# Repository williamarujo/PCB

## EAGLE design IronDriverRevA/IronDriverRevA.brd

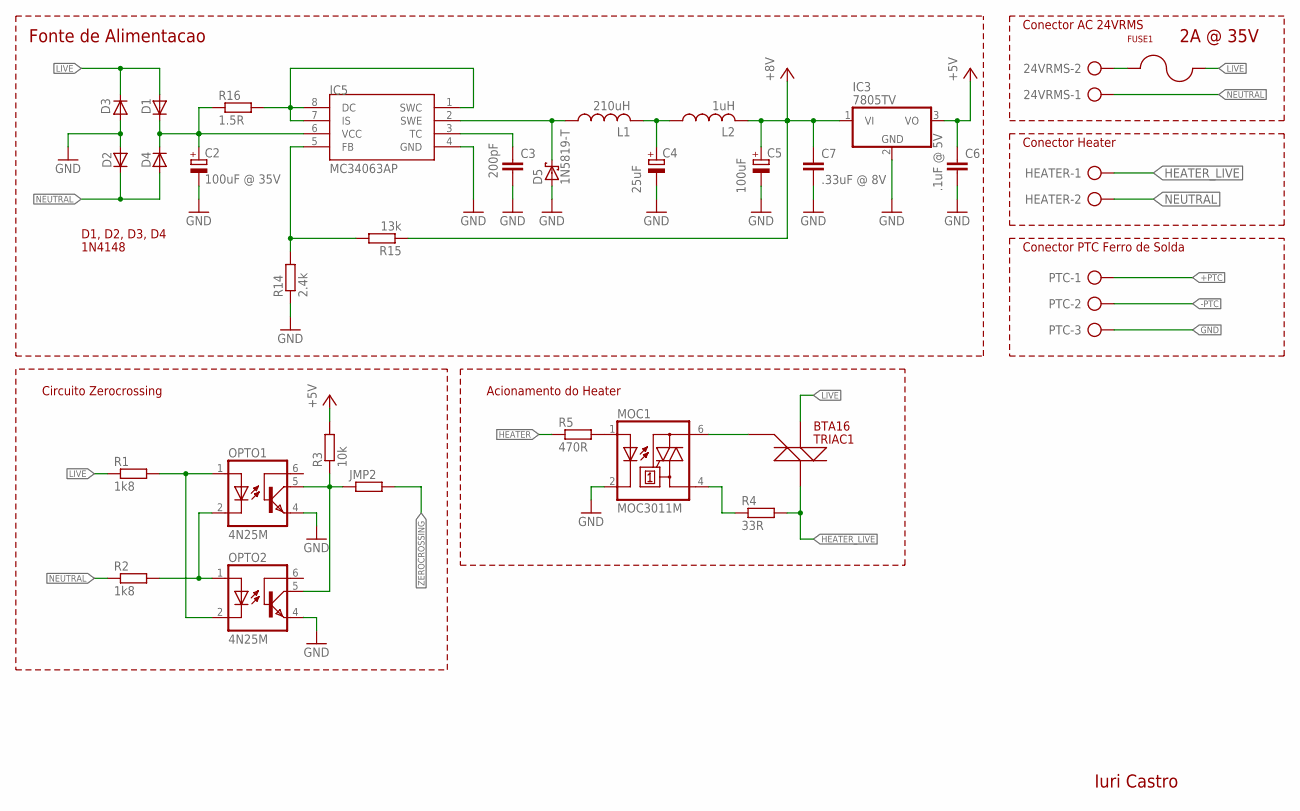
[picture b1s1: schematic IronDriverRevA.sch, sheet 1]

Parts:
24VRMS: AK500/2
C2: 100uF @ 35V; E3,5-8
C3: 200pF; C025-025X050
C4: 25uF; E3,5-8
C5: 100uF; E3,5-8
C6: .1uF @ 5V; C025-025X050
C7: .33uF @ 8V; C025-025X050
D1, D2, D3, D4: 1N4004; DO41-10
D5: 1N5819-T; DO41-7.6
FUSE1: FUSEHOLDER; FUSE32V2A5
HEATER: AK500/2
IC3: 7805TV; TO220V
IC5: MC34063AP; DIL08
JMP2: R-EU_R1206; R1206
L1: 210uH; 6000-XXXX-RC
L2: 1uH; 0204/7
MOC1: MOC3011M; DIL06
OPTO1, OPTO2: 4N25M; DIL06
PTC: AK500/3
R1, R2: 1k8; 0207/7
R3: 10k; 0207/7
R4: 33R; 0207/7
R5: 470R; 0207/7
R14: 2.4k; 0207/7
R15: 13k; 0207/7
R16: 1.5R; 0207/7
TRIAC1: BTA16; TO220V

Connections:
+5V: C6.1, IC3.3 (VO), R3.2; also elsewhere on the board
+8V: C5.+, C7.1, IC3.1 (VI), L2.2, R15.1; also elsewhere on the board
+PTC: PTC.1; also elsewhere on the board
-PTC: PTC.2; also elsewhere on the board
GND: C2.-, C3.2, C4.-, C5.-, C6.2, C7.2, D2.A, D3.A, D5.A, IC3.2 (GND), IC5.4 (GND), MOC1.2 (C), OPTO1.4 (EMI), OPTO2.4 (EMI), PTC.3, R14.1; also elsewhere on the board
HEATER: R5.1; also elsewhere on the board
HEATER_LIVE: HEATER.1, R4.2, TRIAC1.2 (A2)
LIVE: D1.A, D3.C, FUSE1.P$3, FUSE1.P$4, R1.1, TRIAC1.1 (A1)
unnamed: MOC1.1 (A), R5.2
unnamed: OPTO1.2 (C), OPTO2.1 (A), R2.2
unnamed: OPTO1.1 (A), OPTO2.2 (C), R1.2
unnamed: MOC1.6 (A2), TRIAC1.3 (G)
unnamed: MOC1.4 (A1), R4.1
unnamed: 24VRMS.2, FUSE1.P$1, FUSE1.P$2
unnamed: D5.C, IC5.2 (SWE), L1.1
unnamed: IC5.5 (FB), R14.2, R15.2
unnamed: IC5.1 (SWC), IC5.7 (IS), IC5.8 (DC), R16.2
unnamed: C4.+, L1.2, L2.1
unnamed: C3.1, IC5.3 (TC)
unnamed: C2.+, D1.C, D4.C, IC5.6 (VCC), R16.1
NEUTRAL: 24VRMS.1, D2.C, D4.A, HEATER.2, R2.1
ZEROCROSSING: JMP2.2; also elsewhere on the board
ZEROCROSSING_B: JMP2.1, OPTO1.5 (COL), OPTO2.5 (COL), R3.1

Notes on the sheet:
Conector AC 24VRMS
Conector PTC Ferro de Solda
Conector Heater
Circuito Zerocrossing
Acionamento do Heater
D1, D2, D3, D4
1N4148
Iuri Castro
2A @ 35V
Fonte de Alimentacao

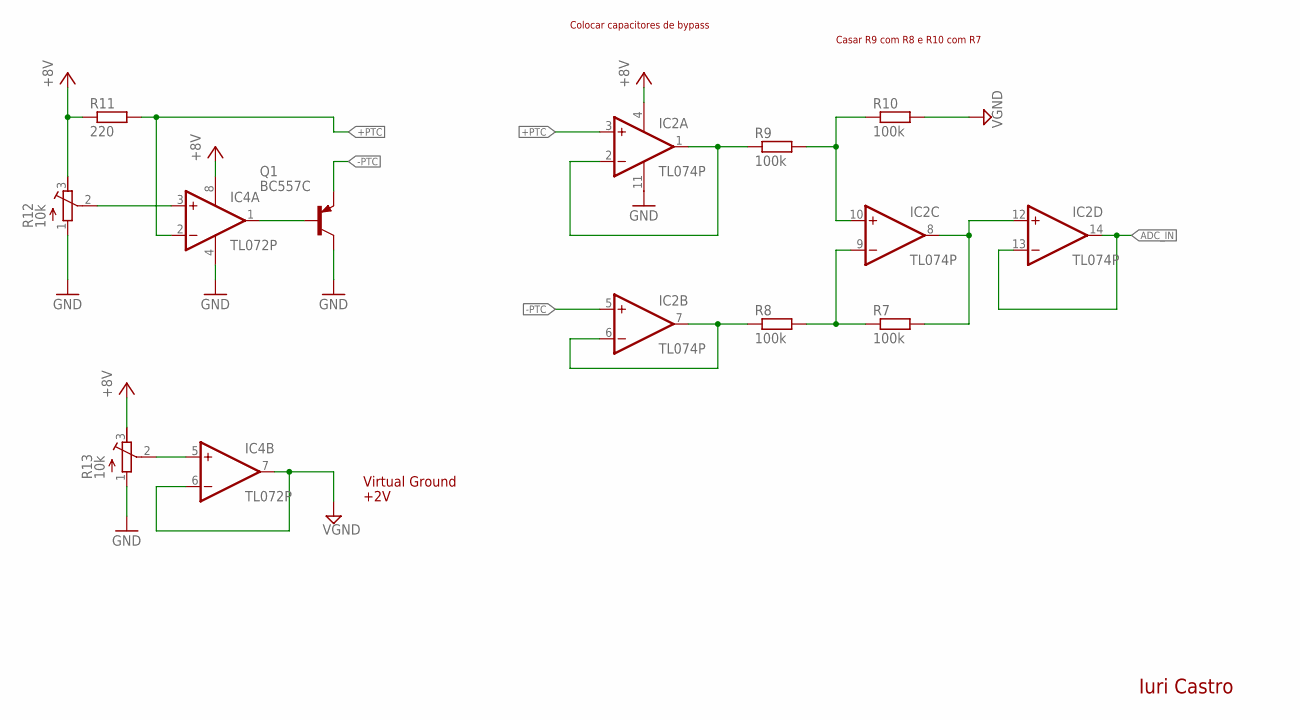
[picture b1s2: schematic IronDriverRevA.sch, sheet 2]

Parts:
IC2: TL074P; DIL14
IC4: TL072P; DIL08
Q1: BC557C; TO92-EBC
R7, R8, R9, R10: 100k; 0207/7
R11: 220; 0207/7
R12, R13: 10k; RTRIM3296W

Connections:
+8V: IC2.4 (V+), IC4.8 (V+), R11.1, R12.3 (E), R13.3 (E); also elsewhere on the board
+PTC: IC2.3 (+IN), IC4.2 (-IN), R11.2; also elsewhere on the board
-PTC: IC2.5 (+IN), Q1.E; also elsewhere on the board
ADC_IN: IC2.13 (-IN), IC2.14 (OUT); also elsewhere on the board
GND: IC2.11 (V-), IC4.4 (V-), Q1.C, R12.1 (A), R13.1 (A); also elsewhere on the board
unnamed: IC4.1 (OUT), Q1.B
unnamed: IC2.9 (-IN), R7.1, R8.2
unnamed: IC2.10 (+IN), R9.2, R10.1
unnamed: IC4.5 (+IN), R13.2 (S)
unnamed: IC2.1 (OUT), IC2.2 (-IN), R9.1
unnamed: IC2.6 (-IN), IC2.7 (OUT), R8.1
unnamed: IC2.8 (OUT), IC2.12 (+IN), R7.2
unnamed: IC4.3 (+IN), R12.2 (S)
VGND: IC4.6 (-IN), IC4.7 (OUT), R10.2; also elsewhere on the board

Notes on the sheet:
Virtual Ground
+2V
Casar R9 com R8 e R10 com R7
Colocar capacitores de bypass
Iuri Castro

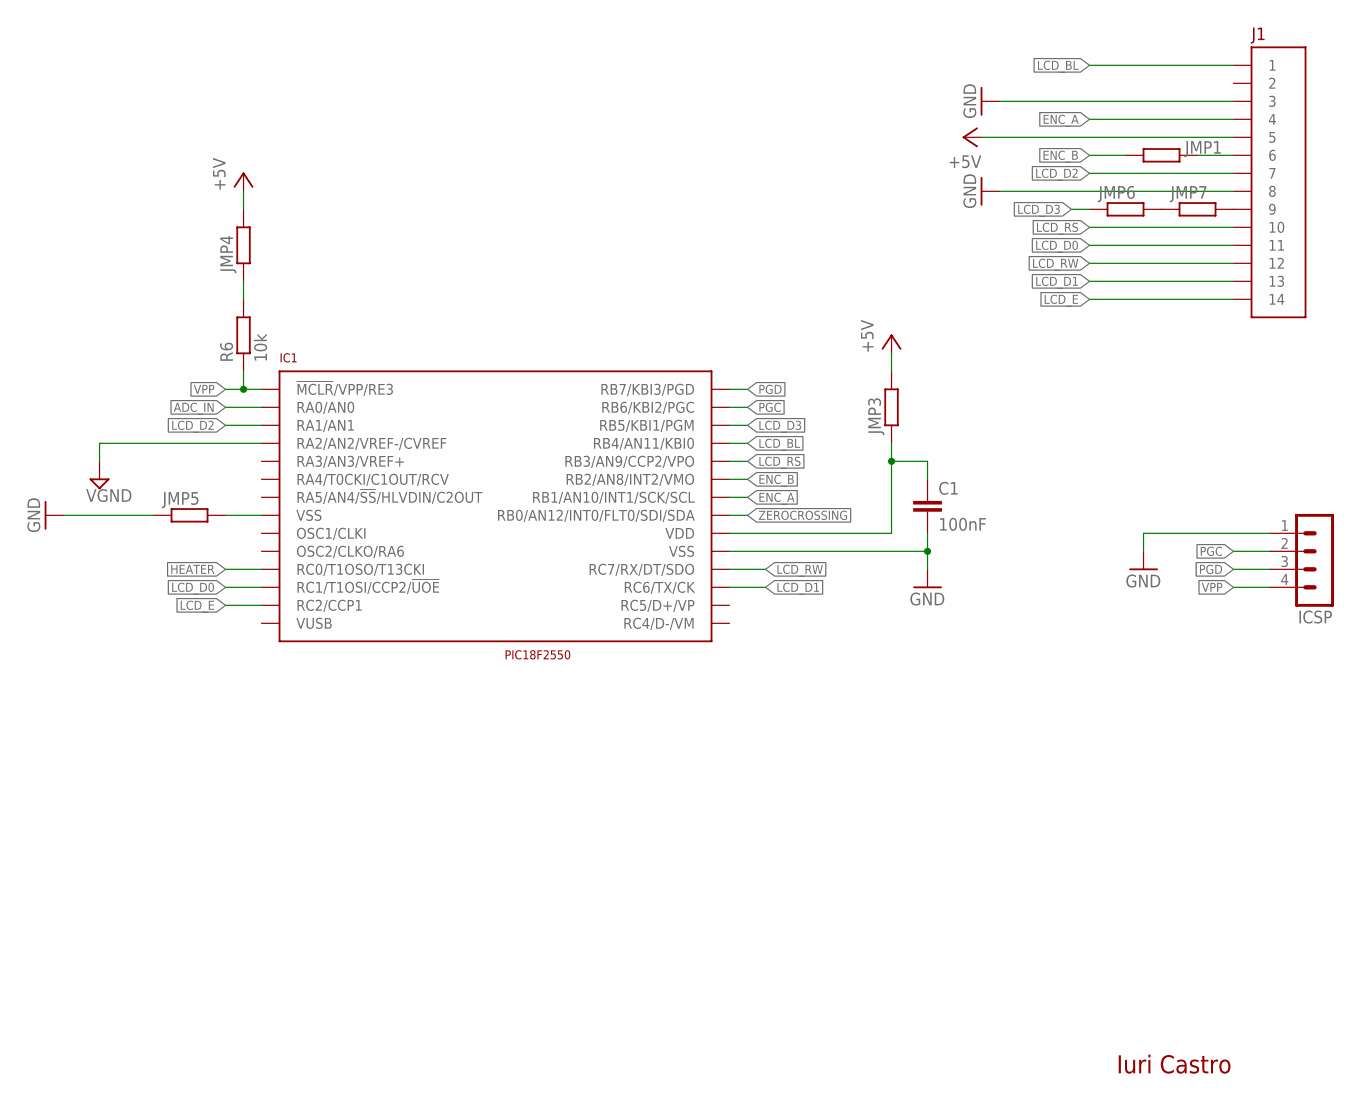
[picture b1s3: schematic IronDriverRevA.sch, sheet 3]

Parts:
C1: 100nF; C0805
IC1: PIC18F2550; DIL28-3
ICSP: MA04-1
J1: FFC14X1
JMP1, JMP3, JMP4, JMP5, JMP6, JMP7: R-EU_R1206; R1206
R6: 10k; 0207/7

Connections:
+5V: JMP3.2, JMP4.2; also elsewhere on the board
+5V_JMP4: J1.P$5 (5), JMP4.1, R6.2
+5V_MC: C1.1, IC1.20 (VDD), JMP3.1
ADC_IN: IC1.2 (RA0/AN0); also elsewhere on the board
ENC_A: IC1.22 (RB1/AN10/INT1/SCK/SCL), J1.P$4 (4)
ENC_B: IC1.23 (RB2/AN8/INT2/VMO), JMP1.1
GND: C1.2, IC1.8 (VSS), IC1.19 (VSS), ICSP.1, J1.P$8 (8), JMP5.2; also elsewhere on the board
GND_JMP5: J1.P$3 (3), JMP5.1
HEATER: IC1.11 (RC0/T1OSO/T13CKI); also elsewhere on the board
LCD_BL: IC1.25 (RB4/AN11/KBI0), J1.P$1 (1)
LCD_D0: IC1.12 (RC1/T1OSI/CCP2/!UOE), J1.P$11 (11)
LCD_D1: IC1.17 (RC6/TX/CK), J1.P$13 (13)
LCD_D2: IC1.3 (RA1/AN1), J1.P$7 (7)
LCD_D3: IC1.26 (RB5/KBI1/PGM), JMP6.1
LCD_E: IC1.13 (RC2/CCP1), J1.P$14 (14)
LCD_RS: IC1.24 (RB3/AN9/CCP2/VPO), J1.P$10 (10)
LCD_RW: IC1.18 (RC7/RX/DT/SDO), J1.P$12 (12)
unnamed: J1.P$6 (6), JMP1.2
unnamed: J1.P$9 (9), JMP7.2
unnamed: JMP6.2, JMP7.1
PGC: IC1.27 (RB6/KBI2/PGC), ICSP.2
PGD: IC1.28 (RB7/KBI3/PGD), ICSP.3
VGND: IC1.4 (RA2/AN2/VREF-/CVREF); also elsewhere on the board
VPP: IC1.1 (!MCLR!/VPP/RE3), ICSP.4, R6.1
ZEROCROSSING: IC1.21 (RB0/AN12/INT0/FLT0/SDI/SDA); also elsewhere on the board

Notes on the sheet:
Iuri Castro

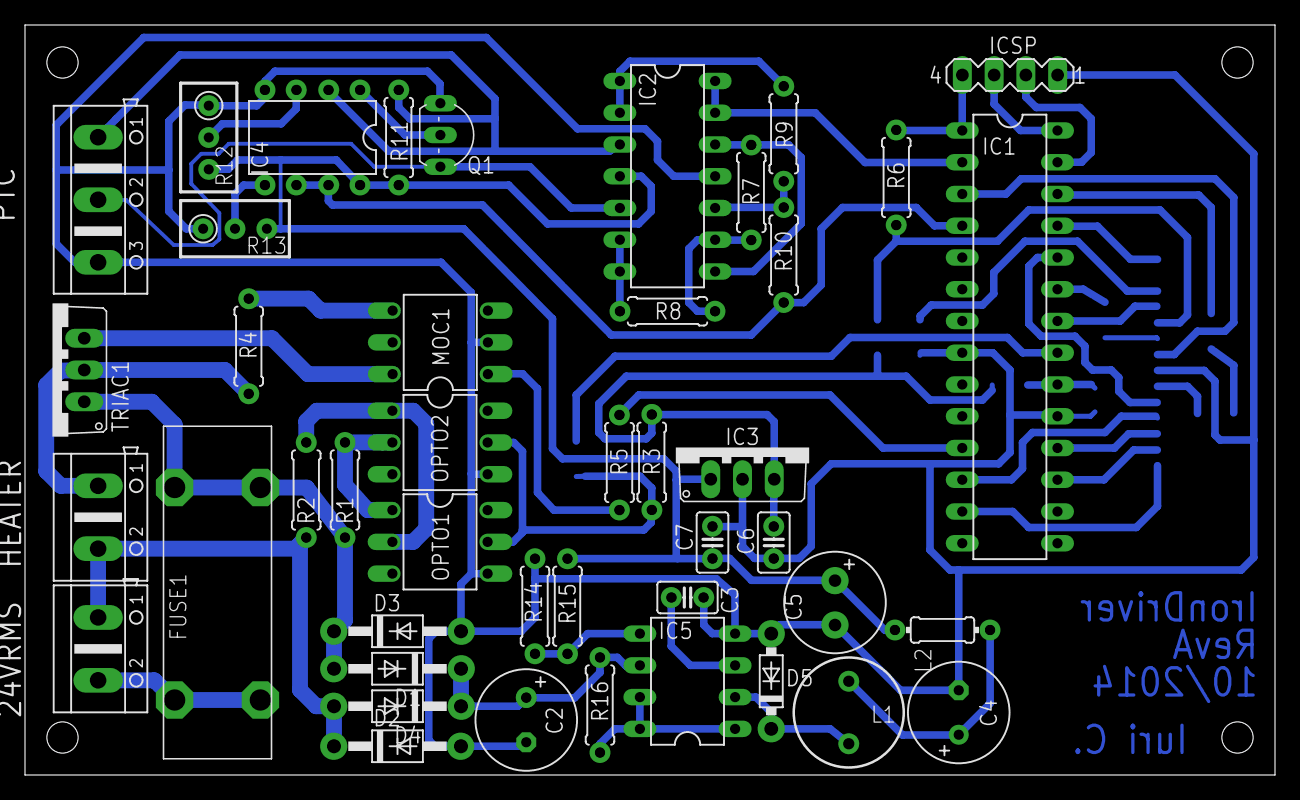
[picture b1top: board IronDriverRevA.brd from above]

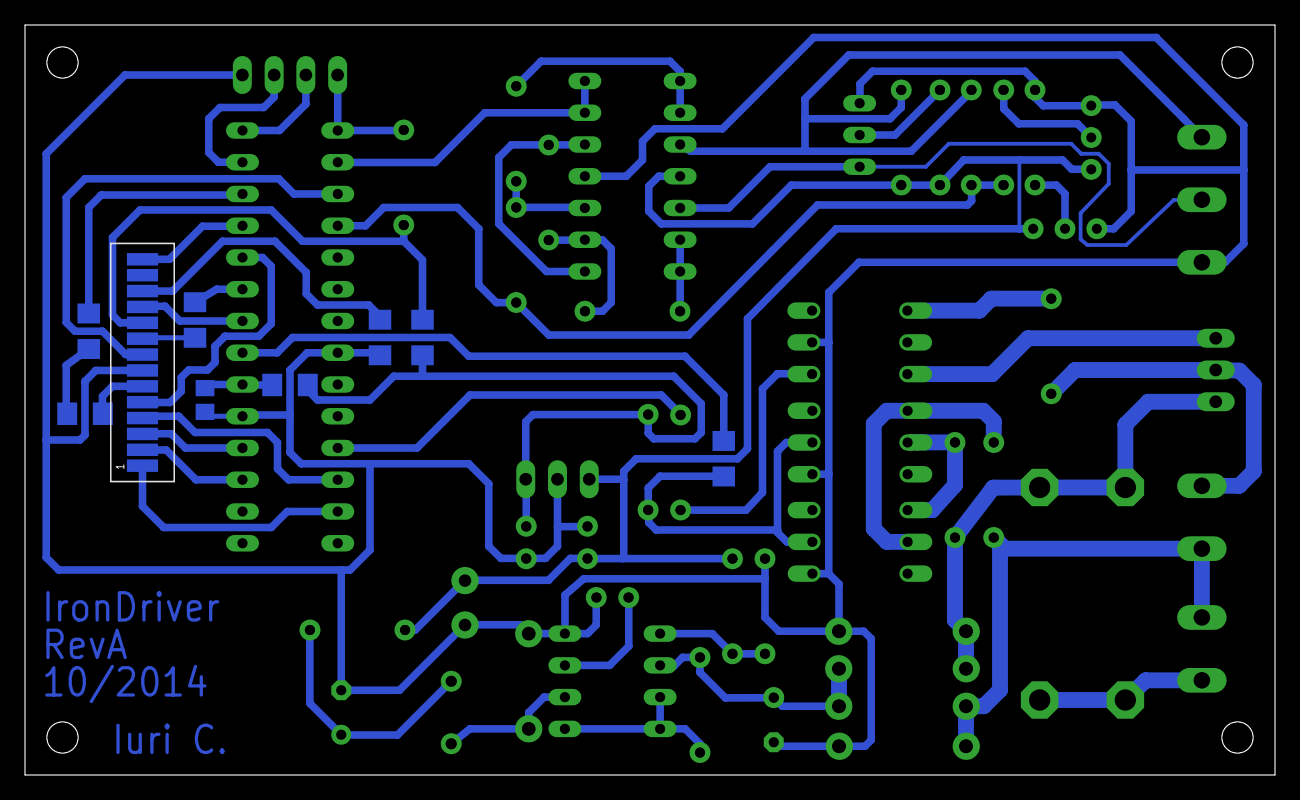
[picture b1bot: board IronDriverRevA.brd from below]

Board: 2 copper layers, 100.0 x 60.0 mm, 53 parts (9 on the bottom side), 52 nets.

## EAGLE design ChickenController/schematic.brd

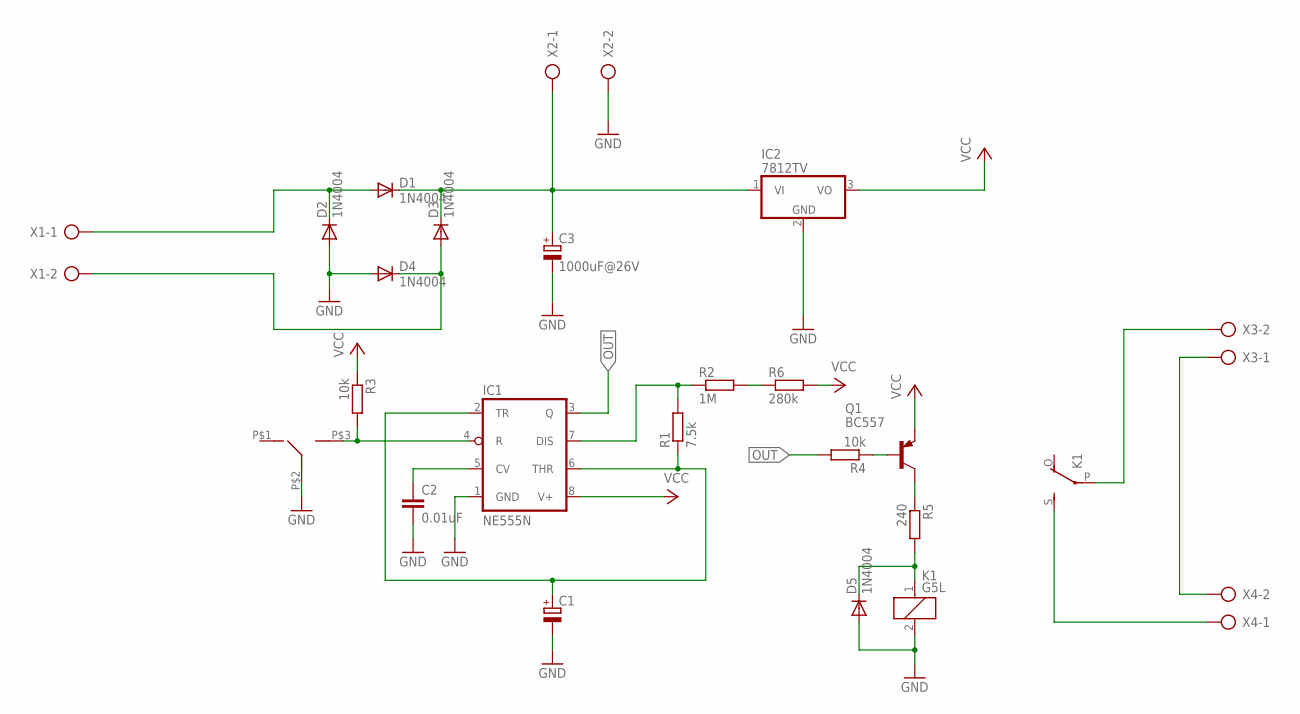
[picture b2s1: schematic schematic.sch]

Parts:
C1: CPOL-EUE5-13; E5-13
C2: 0.01uF; C025-025X050
C3: 1000uF@26V; E5-13
D1, D2, D3, D4, D5: 1N4004; DO41-10
IC1: NE555N; DIL08
IC2: 7812TV; TO220V
K1: G5L; G5LE
Q1: BC557; TO92
R1: 7.5k; 0207/7
R2: 1M; 0207/7
R3, R4: 10k; 0207/7
R5: 240; 0207/7
R6: 280k; 0207/7
SW1: SWITCH
X1, X2, X3, X4: AK500/2

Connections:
18VRMS_F: D1.A, D2.C, X1.1
18VRMS_N: D3.A, D4.C, X1.2
GND: C1.-, C2.2, C3.-, D2.A, D4.A, D5.A, IC1.1 (GND), IC2.2 (GND), K1.2, SW1.P$2, X2.2
unnamed: R2.2, R6.1
unnamed: Q1.2 (B), R4.1
unnamed: C3.+, D1.C, D3.C, IC2.1 (VI), X2.1
unnamed: C1.+, IC1.2 (TR), IC1.6 (THR), R1.1
unnamed: IC1.7 (DIS), R1.2, R2.1
unnamed: IC1.4 (R), R3.2, SW1.P$3
unnamed: C2.1, IC1.5 (CV)
unnamed: K1.S, X4.1
unnamed: Q1.3 (C), R5.1
unnamed: D5.C, K1.1, R5.2
unnamed: X3.1, X4.2
unnamed: K1.P, X3.2
OUT: IC1.3 (Q), R4.2
VCC: IC1.8 (V+), IC2.3 (VO), Q1.1 (E), R3.1, R6.2

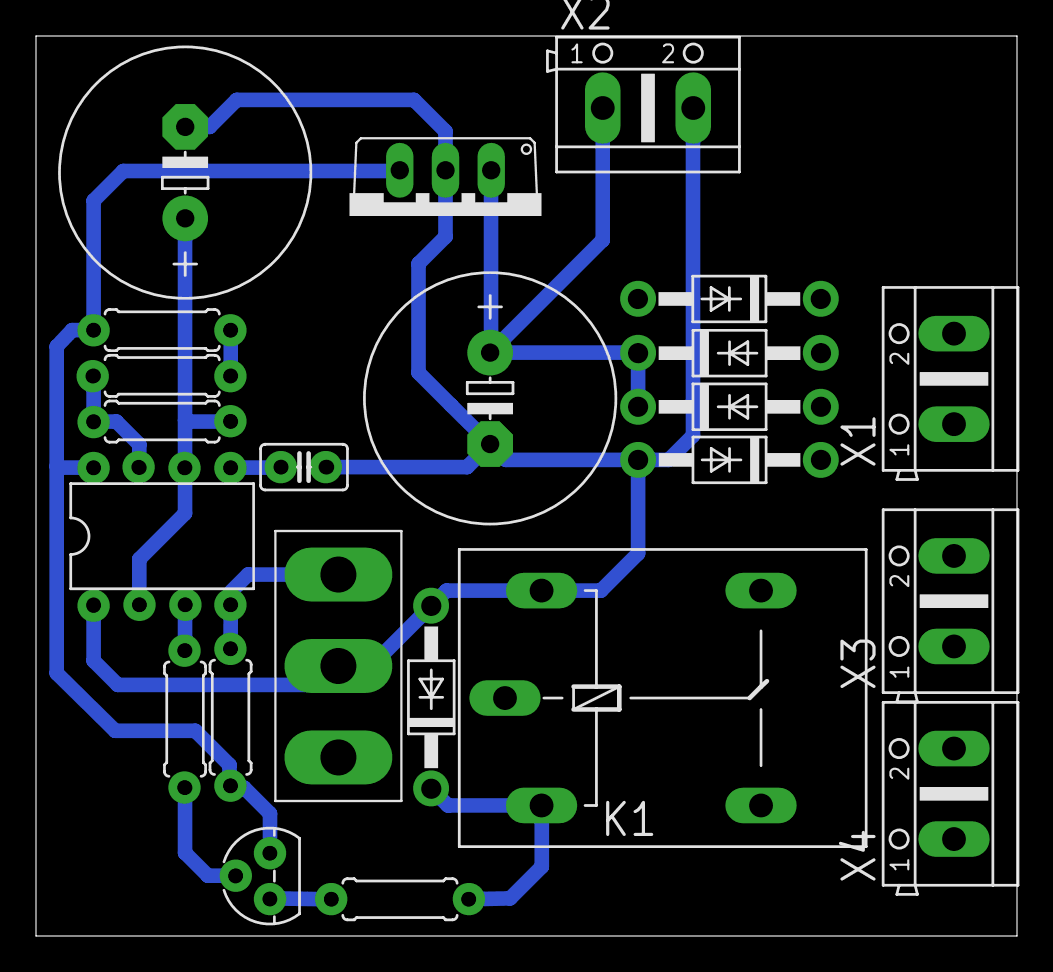
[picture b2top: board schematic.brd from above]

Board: 2 copper layers, 54.5 x 50.0 mm, 23 parts (0 on the bottom side), 17 nets.

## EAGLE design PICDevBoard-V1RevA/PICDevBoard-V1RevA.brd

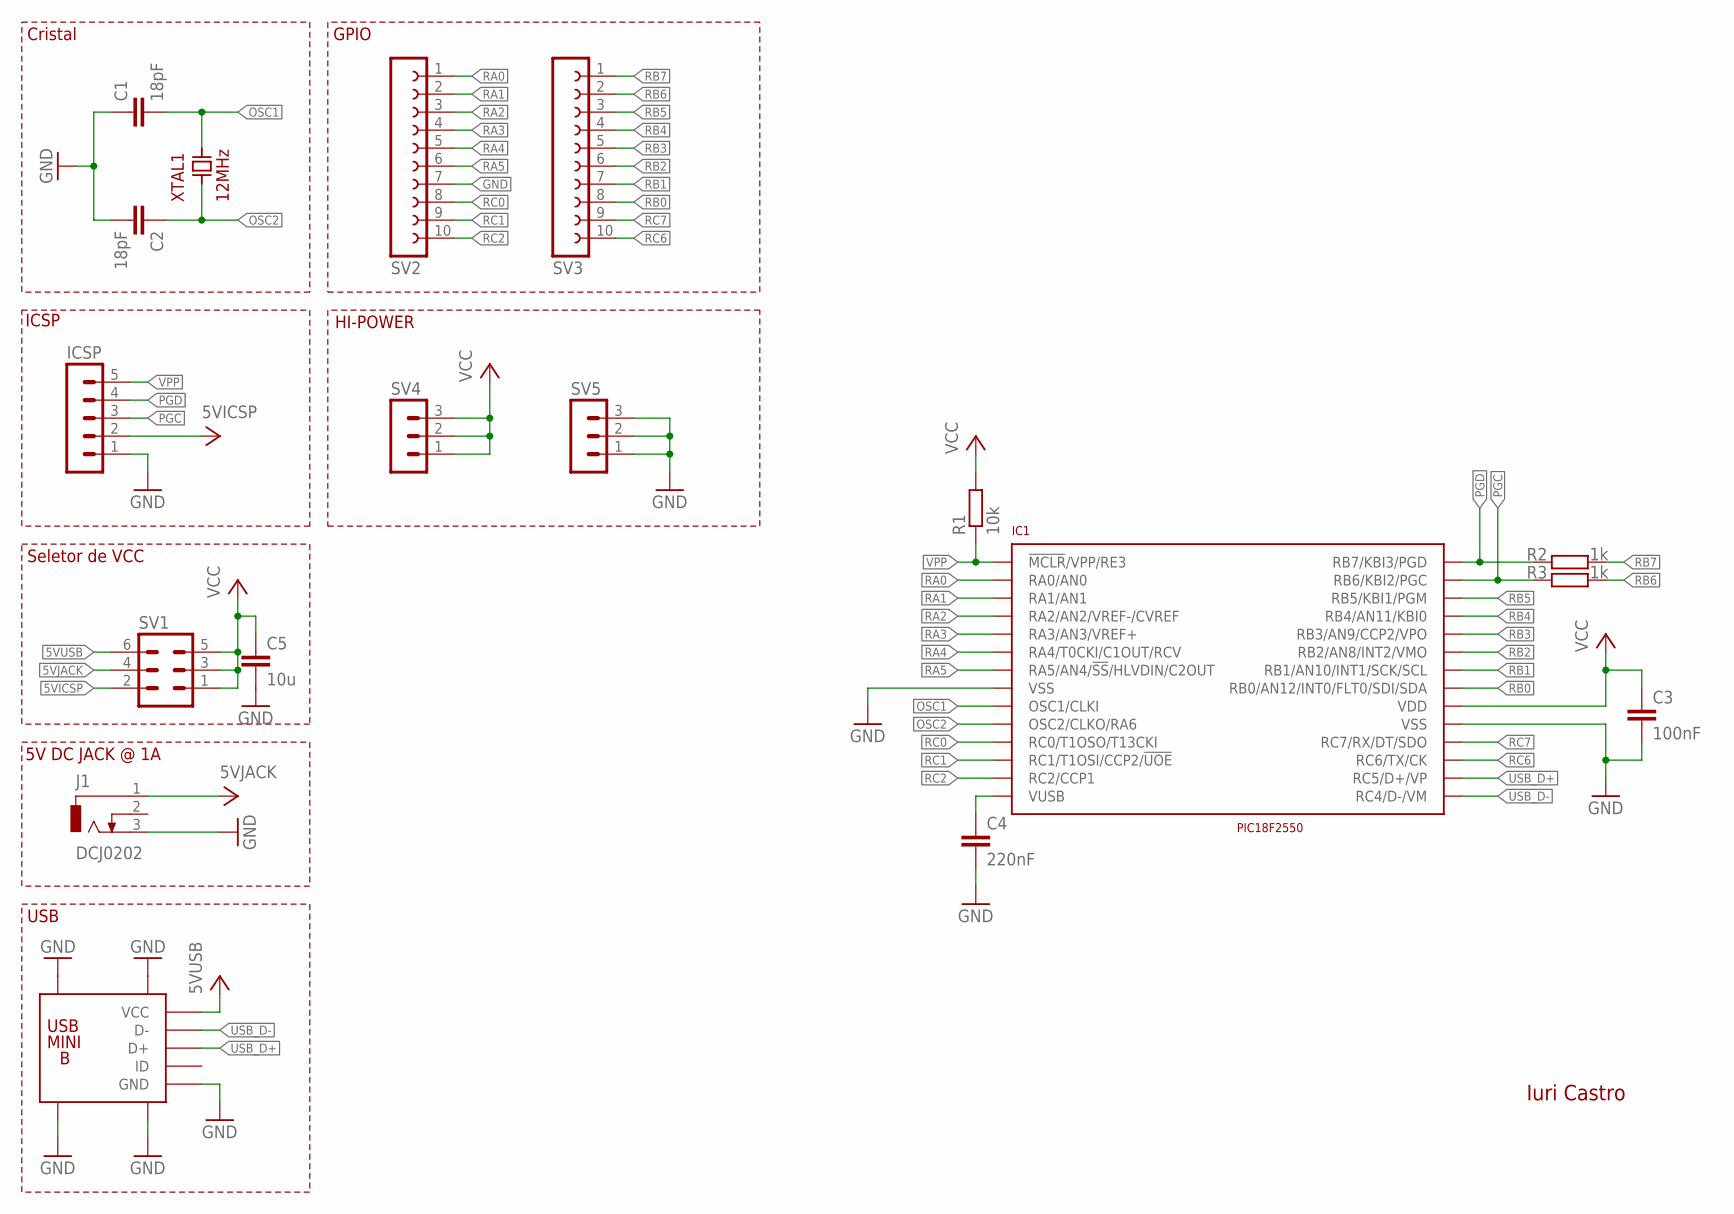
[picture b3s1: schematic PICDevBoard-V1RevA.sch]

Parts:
C1, C2: 18pF; C0805
C3: 100nF; C0805
C4: 220nF; C0805
C5: 10u; C0805
IC1: PIC18F2550; DIL28-3
ICSP: MA05-1
J1: DCJ0202
R1: 10k; R0805
R2, R3: 1k; R0805
SV1: MA03-2
SV2, SV3: FE10-1; FE10
SV4, SV5: MA03-1
USB1: USB-MINI-B; DX2R005HN2E700
XTAL1: 12MHz; HC49-S

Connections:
5VICSP: ICSP.2, SV1.2
5VJACK: J1.1, SV1.4
5VUSB: SV1.6, USB1.P$1 (VCC)
GND: C1.1, C2.2, C3.2, C4.2, C5.2, IC1.8 (VSS), IC1.19 (VSS), ICSP.1, J1.3, SV2.7, SV5.1, SV5.2, SV5.3, USB1.P$5 (GND), USB1.P$6 (GND), USB1.P$7 (GND), USB1.P$8 (GND), USB1.P$9 (GND)
unnamed: C4.1, IC1.14 (VUSB)
OSC1: C1.2, IC1.9 (OSC1/CLKI), XTAL1.P$2
OSC2: C2.1, IC1.10 (OSC2/CLKO/RA6), XTAL1.P$1
PGC: IC1.27 (RB6/KBI2/PGC), ICSP.3, R3.1
PGD: IC1.28 (RB7/KBI3/PGD), ICSP.4, R2.1
RA0: IC1.2 (RA0/AN0), SV2.1
RA1: IC1.3 (RA1/AN1), SV2.2
RA2: IC1.4 (RA2/AN2/VREF-/CVREF), SV2.3
RA3: IC1.5 (RA3/AN3/VREF+), SV2.4
RA4: IC1.6 (RA4/T0CKI/C1OUT/RCV), SV2.5
RA5: IC1.7 (RA5/AN4/!SS!/HLVDIN/C2OUT), SV2.6
RB0: IC1.21 (RB0/AN12/INT0/FLT0/SDI/SDA), SV3.8
RB1: IC1.22 (RB1/AN10/INT1/SCK/SCL), SV3.7
RB2: IC1.23 (RB2/AN8/INT2/VMO), SV3.6
RB3: IC1.24 (RB3/AN9/CCP2/VPO), SV3.5
RB4: IC1.25 (RB4/AN11/KBI0), SV3.4
RB5: IC1.26 (RB5/KBI1/PGM), SV3.3
RB6: R3.2, SV3.2
RB7: R2.2, SV3.1
RC0: IC1.11 (RC0/T1OSO/T13CKI), SV2.8
RC1: IC1.12 (RC1/T1OSI/CCP2/!UOE), SV2.9
RC2: IC1.13 (RC2/CCP1), SV2.10
RC6: IC1.17 (RC6/TX/CK), SV3.10
RC7: IC1.18 (RC7/RX/DT/SDO), SV3.9
USB_D+: IC1.16 (RC5/D+/VP), USB1.P$3 (D+)
USB_D-: IC1.15 (RC4/D-/VM), USB1.P$2 (D-)
VCC: C3.1, C5.1, IC1.20 (VDD), R1.2, SV1.1, SV1.3, SV1.5, SV4.1, SV4.2, SV4.3
VPP: IC1.1 (!MCLR!/VPP/RE3), ICSP.5, R1.1

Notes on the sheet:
Seletor de VCC
ICSP
5V DC JACK @ 1A
USB
Cristal
GPIO
HI-POWER
Iuri Castro

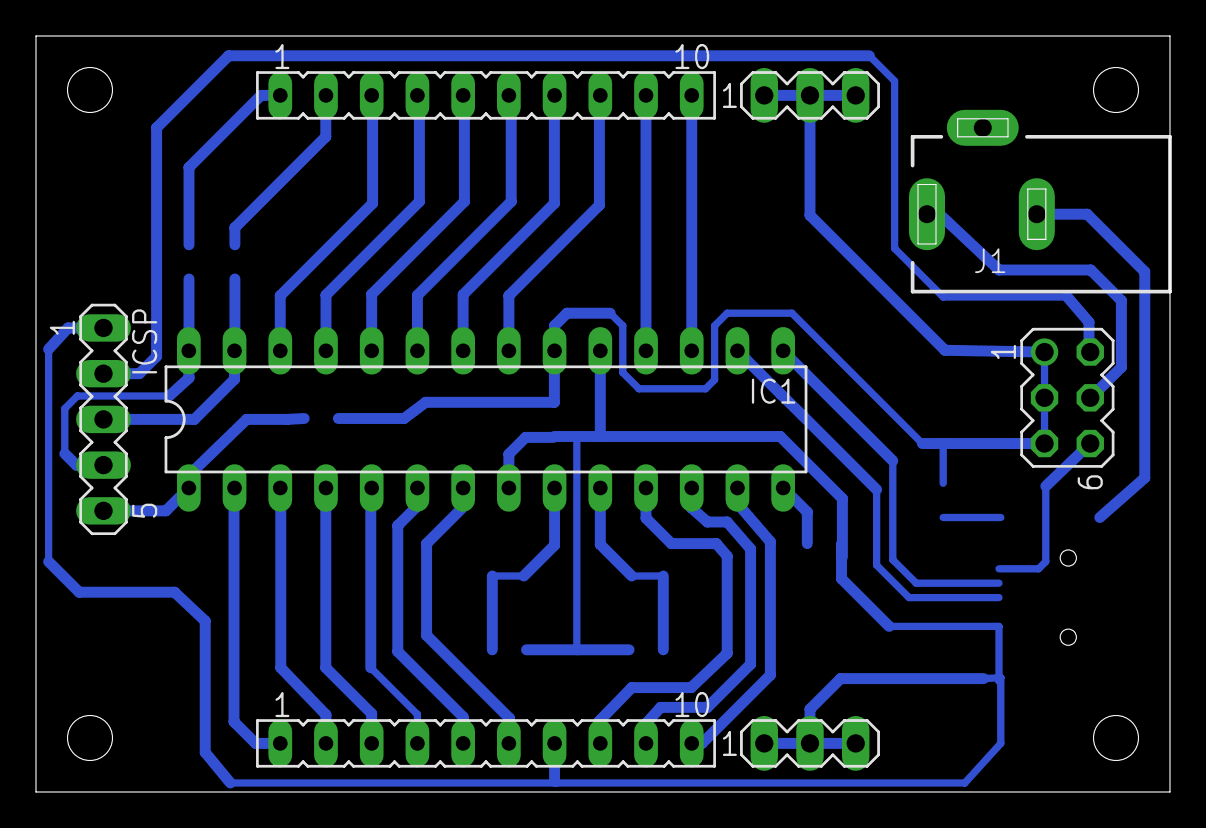
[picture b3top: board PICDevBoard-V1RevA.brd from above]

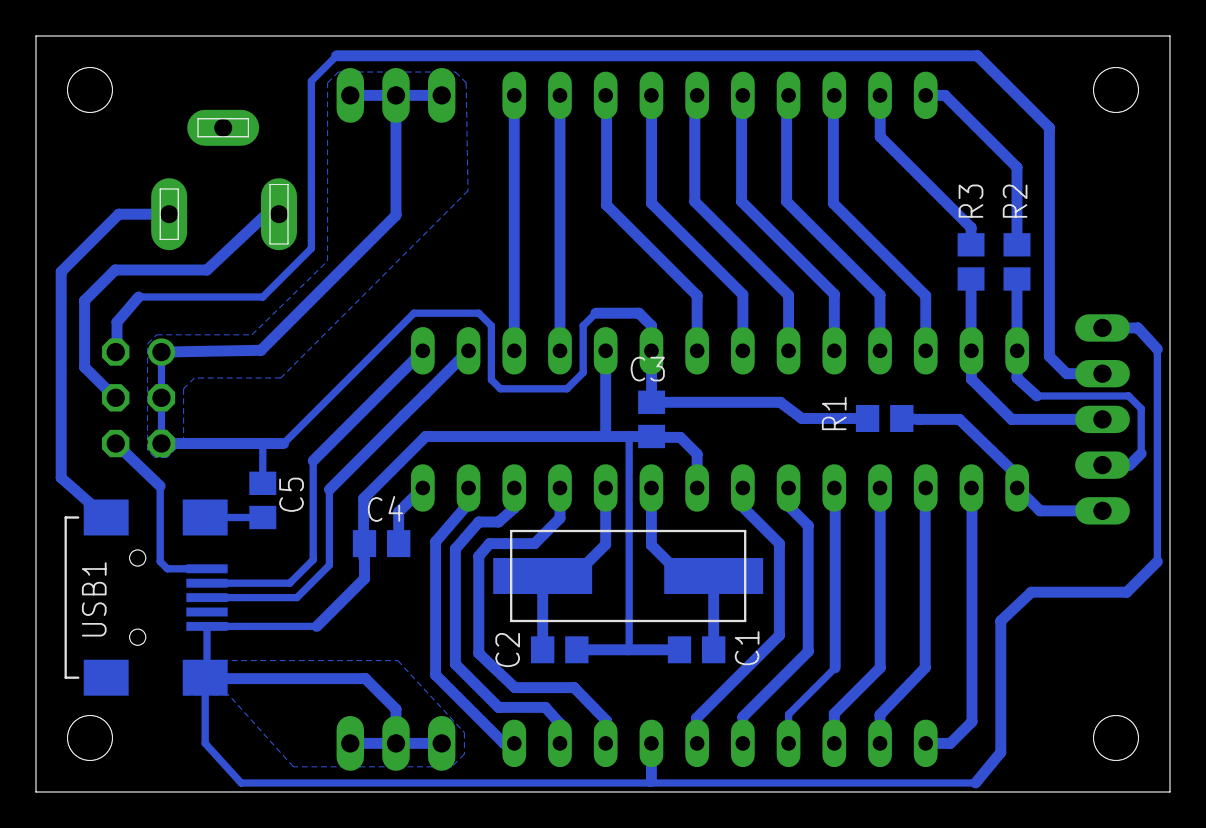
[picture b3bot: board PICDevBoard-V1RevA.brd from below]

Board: 2 copper layers, 63.0 x 42.0 mm, 18 parts (10 on the bottom side), 32 nets.

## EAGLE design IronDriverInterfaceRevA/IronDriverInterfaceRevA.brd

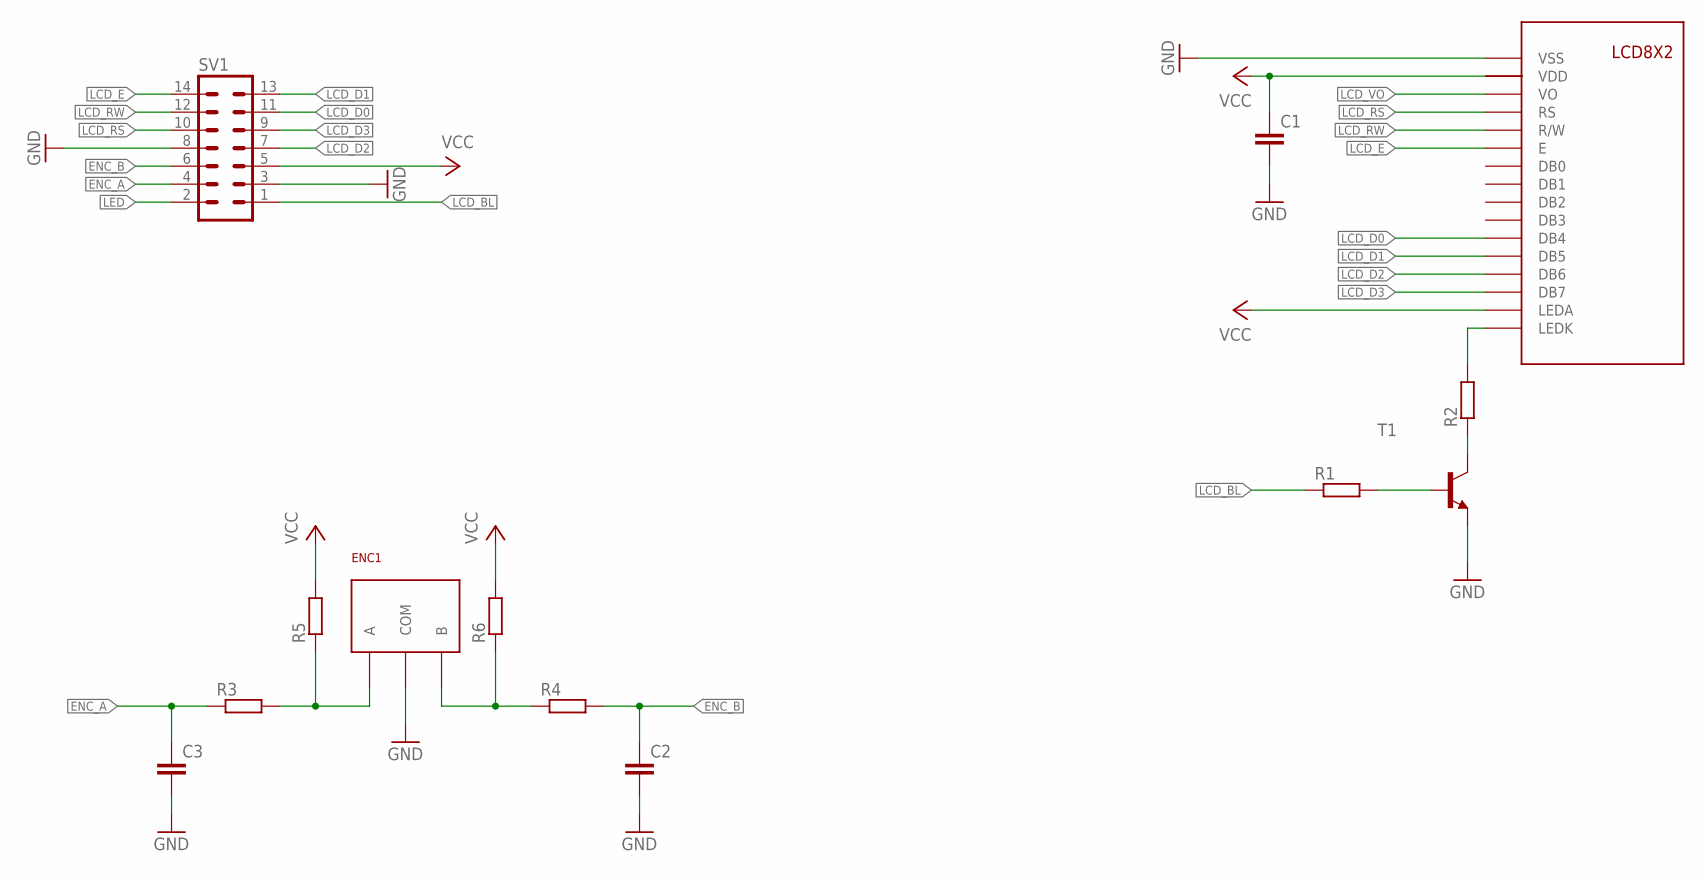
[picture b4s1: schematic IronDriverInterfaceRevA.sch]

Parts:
C1, C2, C3: C-EUC0805; C0805
ENC1: ENCODER; ENCODER_FOOTPRINT
LCD1: HC0821; LCD0821_FOOTPRINT
R1, R2, R3, R4, R5, R6: R-EU_R0805; R0805
SV1: MA07-2
T1: MMBT3904LT1-NPN-SOT23-BEC; SOT23-BEC

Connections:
ENC_A: C3.1, R3.1, SV1.4
ENC_B: C2.1, R4.2, SV1.6
GND: C1.2, C2.2, C3.2, ENC1.P$2 (COM), LCD1.P$1 (VSS), SV1.3, SV1.8, T1.E
LCD_BL: R1.1, SV1.1
LCD_D0: LCD1.P$11 (DB4), SV1.11
LCD_D1: LCD1.P$12 (DB5), SV1.13
LCD_D2: LCD1.P$13 (DB6), SV1.7
LCD_D3: LCD1.P$14 (DB7), SV1.9
LCD_E: LCD1.P$6 (E), SV1.14
LCD_RS: LCD1.P$4 (RS), SV1.10
LCD_RW: LCD1.P$5 (R/W), SV1.12
LCD_VO: LCD1.P$3 (VO)
LED: SV1.2
unnamed: LCD1.P$16 (LEDK), R2.2
unnamed: R2.1, T1.C
unnamed: R1.2, T1.B
unnamed: ENC1.P$1 (A), R3.2, R5.1
unnamed: ENC1.P$3 (B), R4.1, R6.1
VCC: C1.1, LCD1.P$2 (VDD), LCD1.P$15 (LEDA), R5.2, R6.2, SV1.5

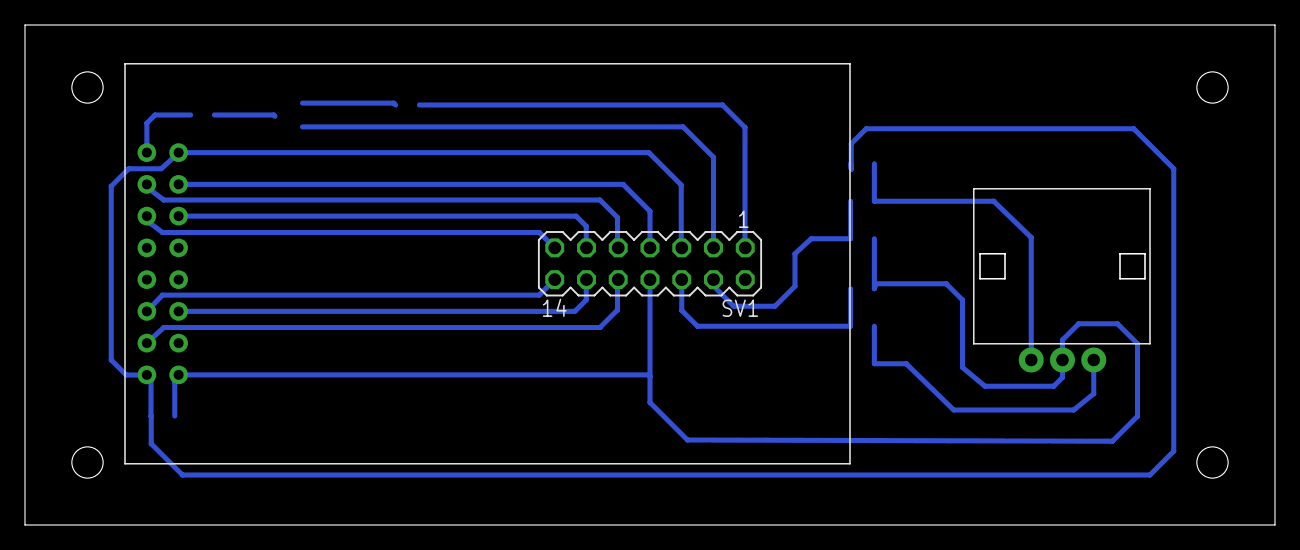
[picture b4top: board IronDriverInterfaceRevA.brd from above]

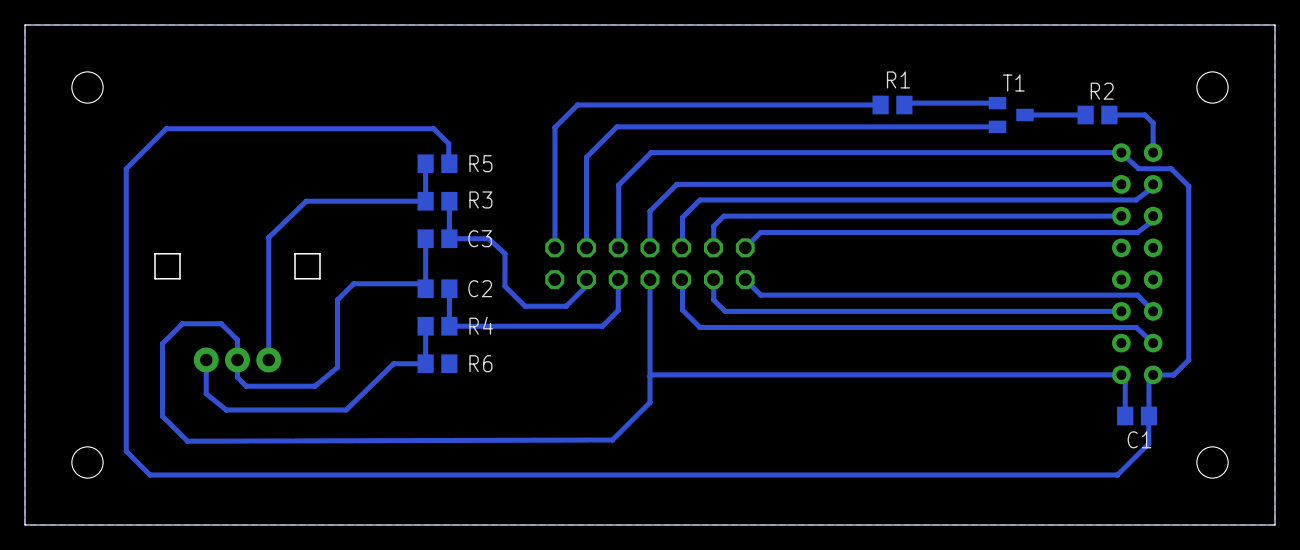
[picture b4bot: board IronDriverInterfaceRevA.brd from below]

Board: 2 copper layers, 99.9 x 39.9 mm, 13 parts (10 on the bottom side), 17 nets.

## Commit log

2014-09-09 :boom::camel: Added .gitattributes & .gitignore files
2014-09-09 Projeto DevBoard e Library
    Arquivos do projeto DevBoard v0.0
2014-09-09 Silk
    Adicionado nome dos pinos no silk (top layer)
2014-09-09 Routing
    Continuação do roteamento
2014-09-10 Routing
    Continuação
2014-09-10 Routing
2014-09-10 Configurações
    Atualizado a lista de arquivos para ignorar
2014-09-10 Cleanup
2014-09-10 Atualização do Silk
2014-09-10 Ajuste de trilhas
2014-09-15 Routing IronDriver
2014-10-29 Routing
    DCDC added
2014-10-29 Added ChikenControlelr
2014-10-29 Bug arrumado
2014-10-30 Finalizando Roteamento
2014-10-30 Ajustes de trilhas
2014-10-30 Alterado largura das trilhas
2014-10-30 Ajustes
